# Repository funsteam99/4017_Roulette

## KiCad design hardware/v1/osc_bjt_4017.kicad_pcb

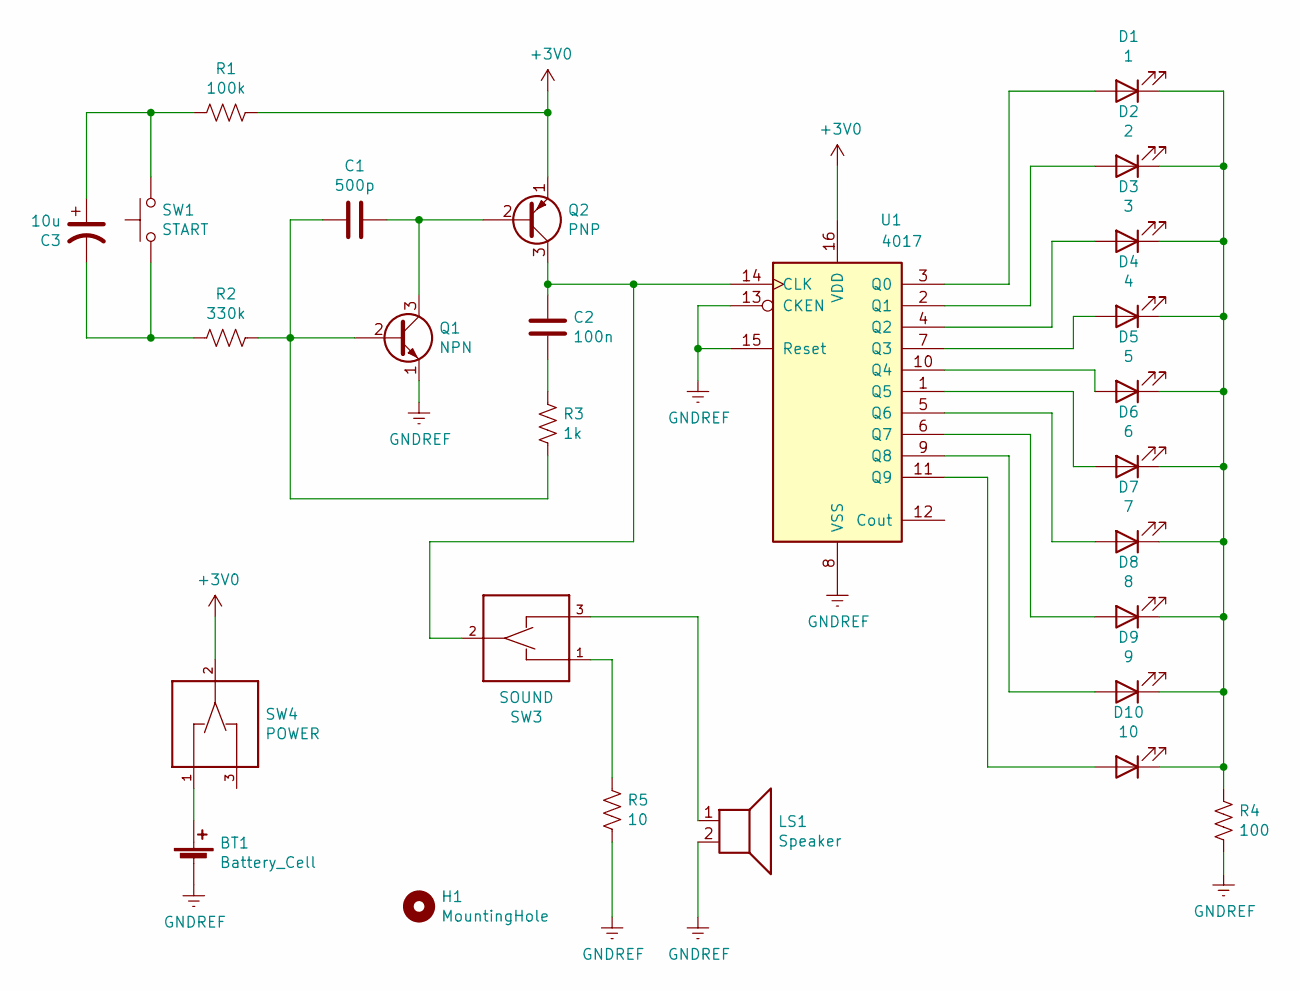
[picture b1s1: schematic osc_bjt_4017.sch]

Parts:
BT1: Battery_Cell; BatteryHolder_Keystone_1058_1x2032
C1: 500p; C_Disc_D7.5mm_W5.0mm_P5.00mm
C2: 100n; C_Disc_D7.5mm_W5.0mm_P5.00mm
C3: 10u; CP_Radial_D5.0mm_P2.50mm
D1: 1; LED_Rectangular_W5.0mm_H2.0mm_Horizontal_O6.35mm_Z1.0mm
D2: 2; LED_Rectangular_W5.0mm_H2.0mm_Horizontal_O6.35mm_Z1.0mm
D3: 3; LED_Rectangular_W5.0mm_H2.0mm_Horizontal_O6.35mm_Z1.0mm
D4: 4; LED_Rectangular_W5.0mm_H2.0mm_Horizontal_O6.35mm_Z1.0mm
D5: 5; LED_Rectangular_W5.0mm_H2.0mm_Horizontal_O6.35mm_Z1.0mm
D6: 6; LED_Rectangular_W5.0mm_H2.0mm_Horizontal_O6.35mm_Z1.0mm
D7: 7; LED_Rectangular_W5.0mm_H2.0mm_Horizontal_O6.35mm_Z1.0mm
D8: 8; LED_Rectangular_W5.0mm_H2.0mm_Horizontal_O6.35mm_Z1.0mm
D9: 9; LED_Rectangular_W5.0mm_H2.0mm_Horizontal_O6.35mm_Z1.0mm
D10: 10; LED_Rectangular_W5.0mm_H2.0mm_Horizontal_O6.35mm_Z1.0mm
H1: MountingHole; MountingHole_3.2mm_M3
LS1: Speaker; MagneticBuzzer_ProjectsUnlimited_AI-4228-TWT-R
Q1: NPN; TO-92L_HandSolder
Q2: PNP; TO-92L_HandSolder
R1: 100k; R_Axial_DIN0309_L9.0mm_D3.2mm_P2.54mm_Vertical
R2: 330k; R_Axial_DIN0309_L9.0mm_D3.2mm_P2.54mm_Vertical
R3: 1k; R_Axial_DIN0309_L9.0mm_D3.2mm_P2.54mm_Vertical
R4: 100; R_Axial_DIN0309_L9.0mm_D3.2mm_P2.54mm_Vertical
R5: 10; R_Axial_DIN0309_L9.0mm_D3.2mm_P2.54mm_Vertical
SW1: START; SW_TH_Tactile_Omron_B3F-10xx
SW3: SOUND; SW_CuK_OS102011MA1QN1_SPDT_Angled
SW4: POWER; SW_CuK_OS102011MA1QN1_SPDT_Angled
U1: 4017; DIP-16_W7.62mm_LongPads

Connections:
+3V0: Q2.1 (E), R1.1, SW4.2, U1.16 (VDD)
GNDREF: BT1.2 (-), LS1.2, Q1.1 (E), R4.2, R5.2, U1.8 (VSS), U1.13 (CKEN), U1.15 (Reset)
unnamed: BT1.1 (+), SW4.1
unnamed: C1.1, Q1.3 (C), Q2.2 (B)
unnamed: C1.2, Q1.2 (B), R2.1, R3.2
unnamed: C2.1, R3.1
unnamed 6: C2.2, Q2.3 (C), SW3.2, U1.14 (CLK); also elsewhere on the board
unnamed: C3.1, R1.2, SW1.2
unnamed: C3.2, R2.2, SW1.1
unnamed: D1.1 (K), D2.1 (K), D3.1 (K), D4.1 (K), D5.1 (K), D6.1 (K), D7.1 (K), D8.1 (K), D9.1 (K), D10.1 (K), R4.1
unnamed: D1.2 (A), U1.3 (Q0)
unnamed: D2.2 (A), U1.2 (Q1)
unnamed: D3.2 (A), U1.4 (Q2)
unnamed: D4.2 (A), U1.7 (Q3)
unnamed: D5.2 (A), U1.10 (Q4)
unnamed: D6.2 (A), U1.1 (Q5)
unnamed: D7.2 (A), U1.5 (Q6)
unnamed: D8.2 (A), U1.6 (Q7)
unnamed: D9.2 (A), U1.9 (Q8)
unnamed: D10.2 (A), U1.11 (Q9)
unnamed 20: LS1.1, SW3.3; also elsewhere on the board
unnamed 21: R5.1, SW3.1; also elsewhere on the board

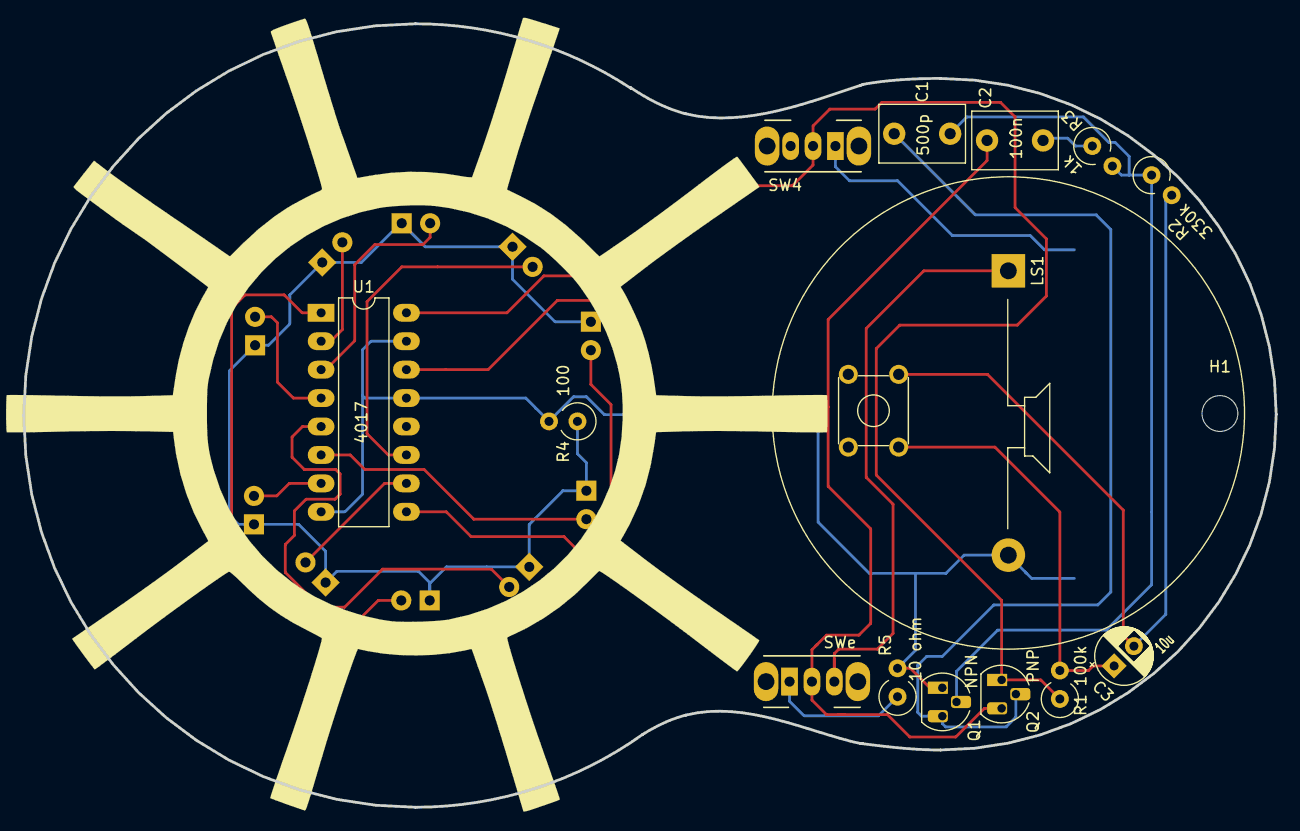
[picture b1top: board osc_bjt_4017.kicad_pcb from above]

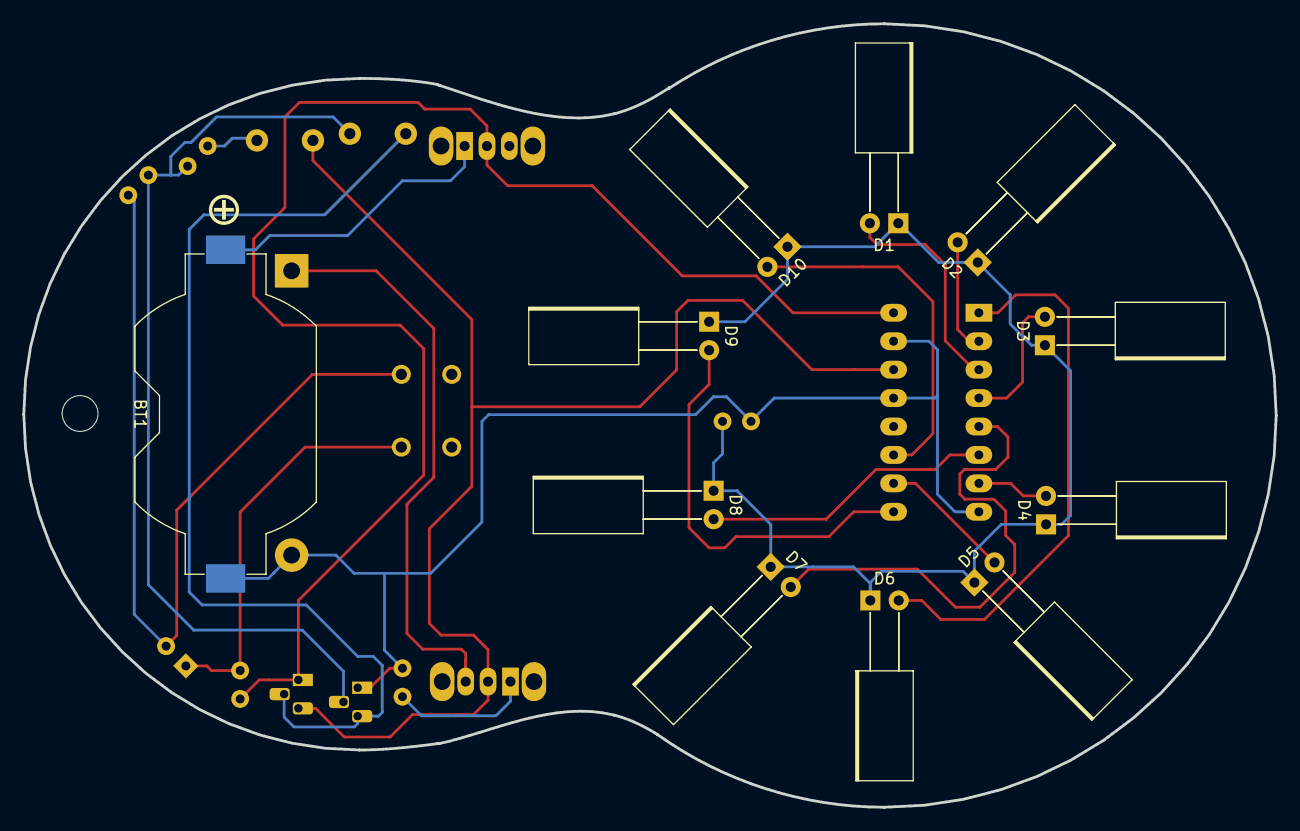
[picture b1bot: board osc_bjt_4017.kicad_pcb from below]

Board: 2 copper layers, 111.9 x 70.0 mm, 27 parts (11 on the bottom side), 22 nets.

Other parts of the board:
SWe: SOUND; SW_CuK_OS102011MA1QN1_SPDT_Angled

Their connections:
unnamed 6: SWe.2; also elsewhere on the board
unnamed 20: SWe.3; also elsewhere on the board
unnamed 21: SWe.1; also elsewhere on the board
